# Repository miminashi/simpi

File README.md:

# simpi

NanoPi NEO carry board with SIM7500 LTE module

## Parts List

- [SIM7500](http://www.cathay.jp/product/lte/sim7500jc.html)
- [Adafruit Powerboost 1000C](https://www.adafruit.com/product/2465)
- [Strawberry Linux TPS63070 可変型昇降圧DC-DCコンバータモジュール(2.5V～9V)](http://strawberry-linux.com/catalog/items?code=16370)
- [NanoPi NEO](http://www.friendlyarm.com/index.php?route=product/product&path=69&product_id=132)

## License

[CC BY-SA 4.0](https://creativecommons.org/licenses/by-sa/4.0/)

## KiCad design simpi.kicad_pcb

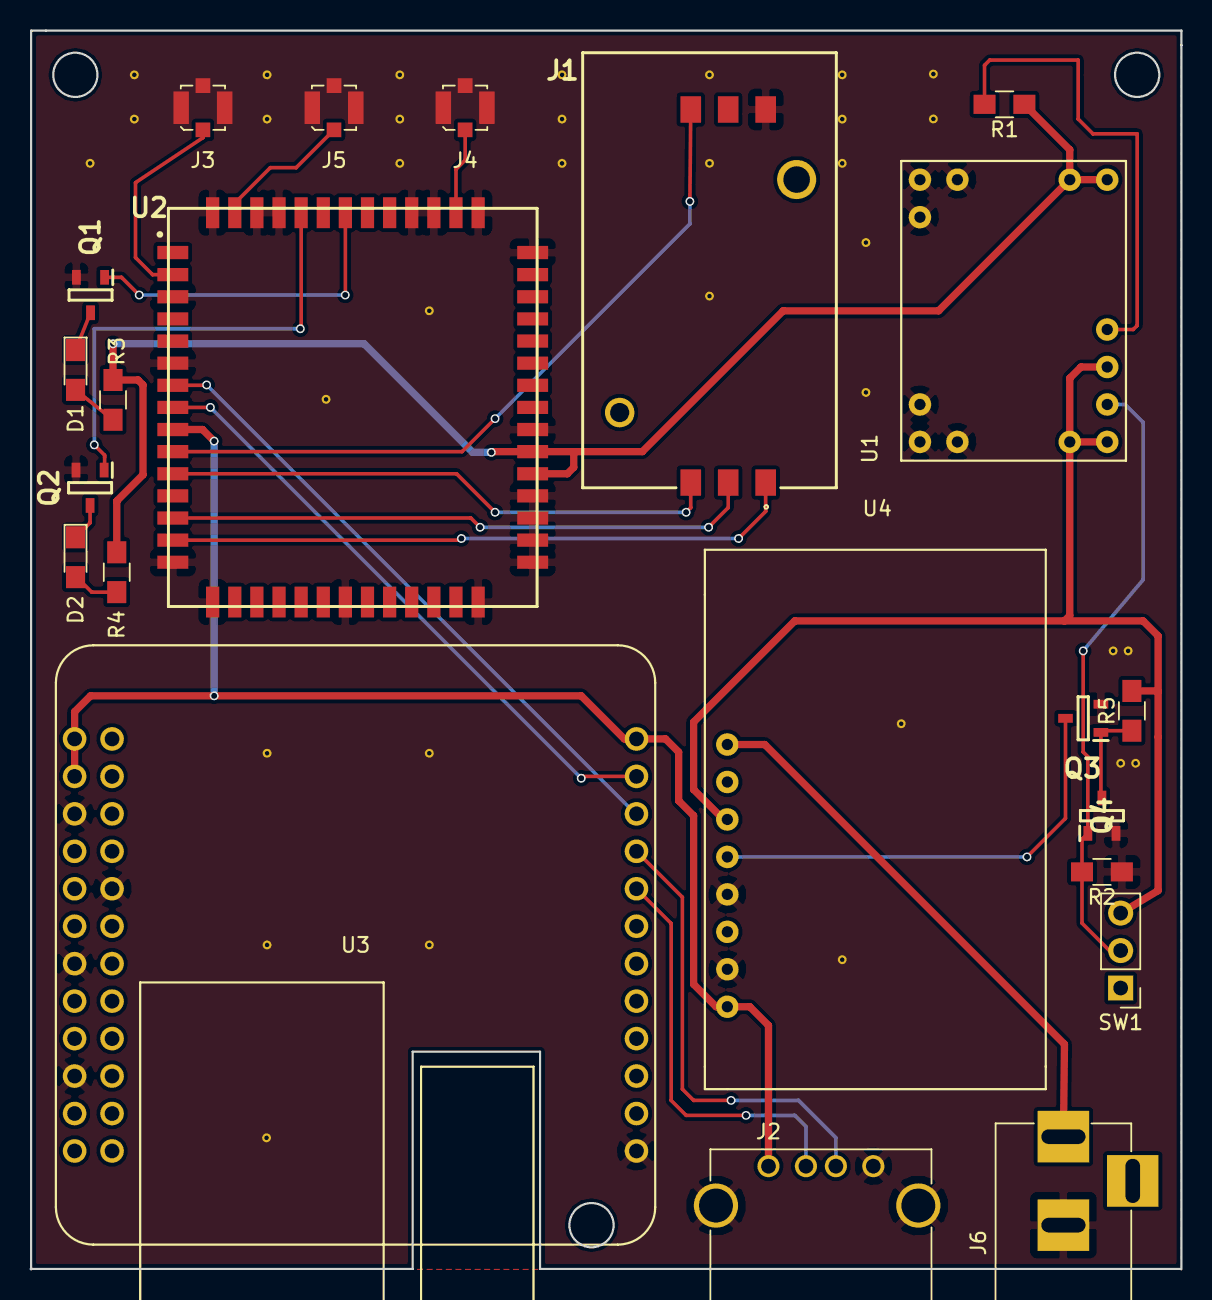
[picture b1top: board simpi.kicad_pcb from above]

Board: 2 copper layers, 78.0 x 84.0 mm, 22 parts (0 on the bottom side), 26 nets.

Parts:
D1: STATUS; LED_0805_HandSoldering
D2: NETLIGHT; LED_0805_HandSoldering
J1: 7111S2015X02LF_SIM_Card_Slot; 7111S2015X02LF
J2: USB_A
J3: DIV_ANT; Molex_Microcoaxial_RF
J4: MAIN_ANT; Molex_Microcoaxial_RF
J5: GNSS_ANT; Molex_Microcoaxial_RF
J6: Jack-DC; BARREL_JACK
Q1, Q2, Q3, Q4: MMUN2233LT1G; SOT96P237X111-3N
R1: 100K; R_0805_HandSoldering
R2, R5: 10K; R_0805_HandSoldering
R3, R4: 360; R_0805_HandSoldering
SW1: PWR_SW; Pin_Header_Straight_1x03_Pitch2.54mm
U1: strawberry_linux_TPS63070_module; strawberry_linux_tps63070_module
U2: SIM7500A; SIM7500A_hand_solder
U3: NanoPiNEO; NanoPi_NEO_upside_down
U4: Adafruit_2465_Powerboost1000C; adafruit_2465_powerboost1000c

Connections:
3V8: R1.1, R3.2, R4.2, U1.6, U2.33, U2.34
+5V: J2.1, U2.9, U3.2, U3.4, U3.25, U4.8
/VBUS: J6.1, U4.1
GND: J1.4, J2.4, J2.5, J3.2, J4.2, J5.2, J6.2, Q1.2, Q2.2, Q3.2, Q4.2, R2.1, U1.1, U1.7, U2.3, U2.6, U2.15, U2.16, U2.22, U2.28, U2.29, U2.30, U2.31, U2.32, U2.35, U2.43, U2.44, U2.46, U2.47, U2.53, U2.54, U2.56, U3.6, U3.9, U3.14, U3.20, U3.36, U4.5, U4.7
unnamed: D1.1, Q1.3
unnamed: D1.2, R3.1
unnamed: D2.1, Q2.3
unnamed: D2.2, R4.1
unnamed: J1.1, U2.14
unnamed: J1.2, U2.13
unnamed: J1.3, U2.11
unnamed: J1.6, U2.10
unnamed: J2.2, U3.29
unnamed: J2.3, U3.28
unnamed: J3.1, U2.2
unnamed: J4.1, U2.45
unnamed: J5.1, U2.55
unnamed: Q1.1, U2.50
unnamed: Q2.1, U2.52
unnamed: Q3.1, Q4.3, R5.1
unnamed: Q3.3, U4.4
unnamed: Q4.1, R2.2, SW1.2, U1.3
unnamed: R1.2, U1.5
unnamed: U2.7, U3.27
unnamed: U2.8, U3.26
VBAT: R5.2, SW1.3, U1.2, U1.4, U4.3

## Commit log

2017-10-09 add screenshot
2017-10-09 smaller screenshot
2017-10-10 modified gitignore
2017-10-10 Adjusted mobule footprints
2017-10-10 fixed transistor model number MMUN2133LT1G -> MMUN2233LT1G
2017-10-10 add gerber
2017-11-26 add Q4 for logic inversion
